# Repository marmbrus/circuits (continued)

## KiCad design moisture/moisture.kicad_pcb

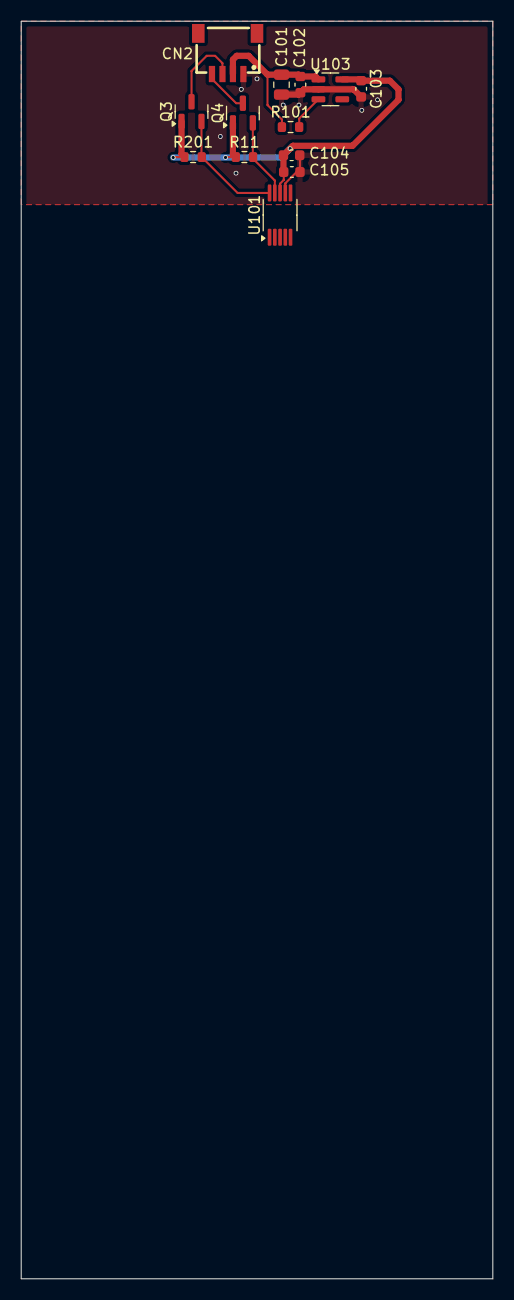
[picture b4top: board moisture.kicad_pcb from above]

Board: 4 copper layers, 45.0 x 120.0 mm, 13 parts (0 on the bottom side), 8 nets.

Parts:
C101: 10uF; C_0805_2012Metric
C102, C103, C104: 1uF; C_0603_1608Metric
C105: 100nF; C_0603_1608Metric
CN2: SM04B-SRSS-TB (LF)(SN); CONN-SMD_4P-P1.00_SM04B-SRSS-TB-LF-SN
Q3, Q4: BSS138; SOT-23
R11, R101, R201: 10k; R_0603_1608Metric
U101: FDC1004DGSR; MSOP-10_3x3mm_P0.5mm
U103: TLV75733PDBV; SOT-23-5

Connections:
/i2c/3V3: C103.1, C104.1, C105.1, Q3.1 (G), Q4.1 (G), R11.1, R201.1, U101.8 (VDD), U103.5 (OUT)
/i2c/5V: C101.1, C102.1, CN2.2, R101.1, U103.1 (IN)
/i2c/GND: C101.2, C102.2, C103.2, C104.2, C105.2, CN2.1, U101.7 (GND), U103.2 (GND)
/i2c/I2C.SCL: Q4.2 (S), R11.2, U101.9 (SCL)
/i2c/I2C.SDA: Q3.2 (S), R201.2, U101.10 (SDA)
unnamed: CN2.3, Q3.3 (D)
unnamed: CN2.4, Q4.3 (D)
unnamed: R101.2, U103.3 (EN)

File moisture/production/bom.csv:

Designator,Footprint,Quantity,Value,LCSC Part #
C101,0805,1,10uF,
"C102, C103, C104",0603,3,1uF,
C105,0603,1,100nF,
CN2,CONN-SMD_4P-P1.00_SM04B-SRSS-TB-LF-SN,1,SM04B-SRSS-TB (LF)(SN),C160404
"Q3, Q4",SOT-23,2,BSS138,
"R101, R11, R201",0603,3,10k,
U103,SOT-23-5,1,TLV75733PDBV,

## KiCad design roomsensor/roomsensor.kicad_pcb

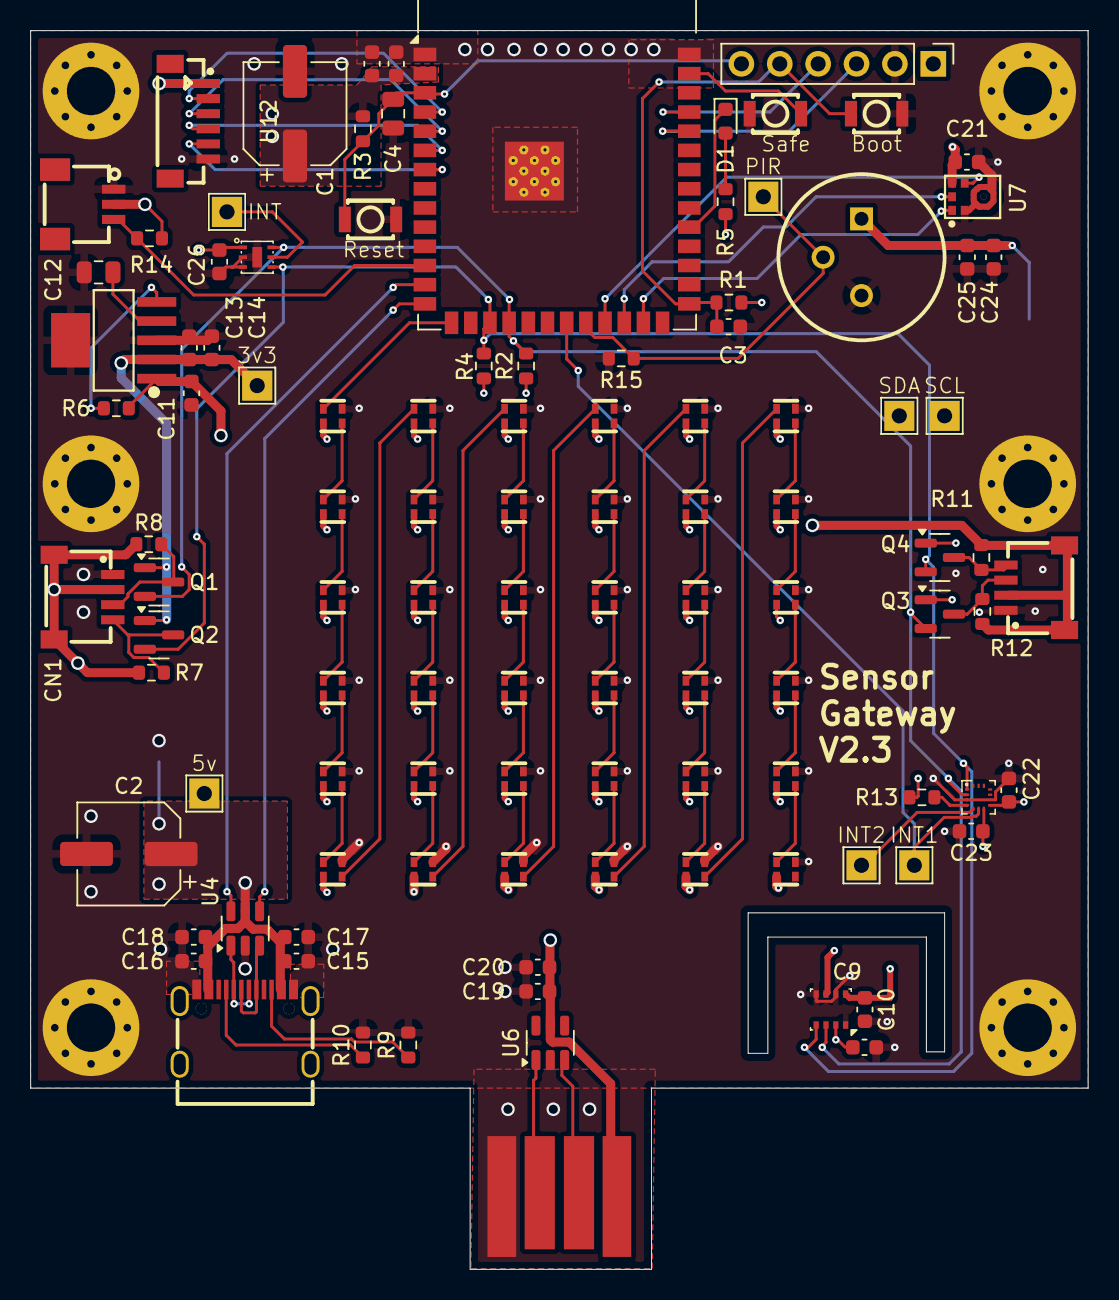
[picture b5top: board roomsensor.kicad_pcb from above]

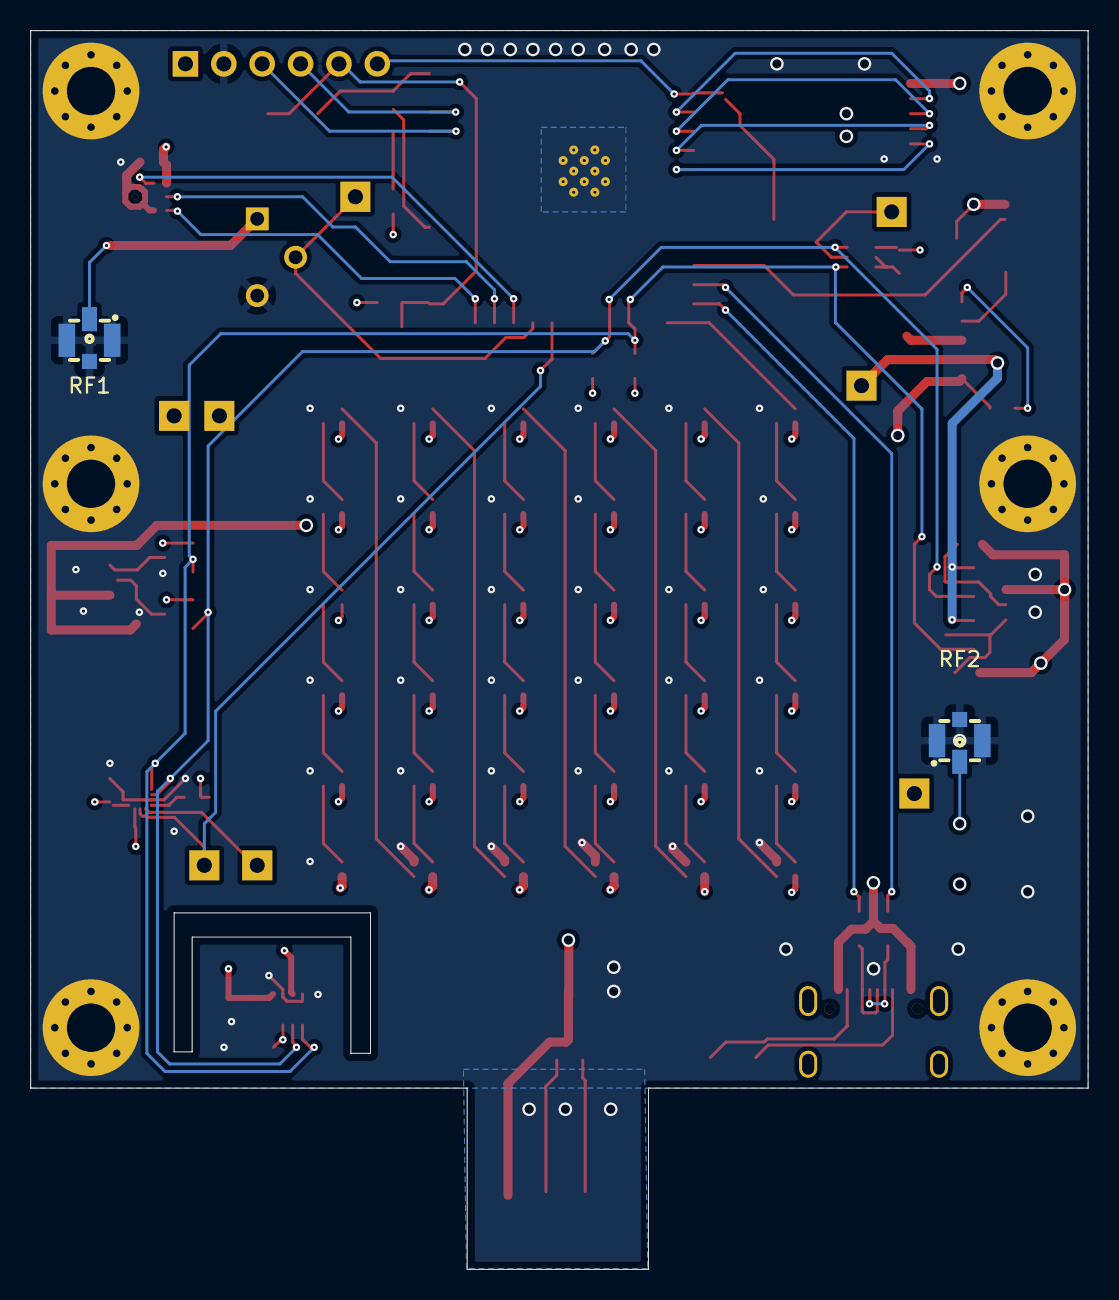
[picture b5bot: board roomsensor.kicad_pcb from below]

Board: 4 copper layers, 70.0 x 82.0 mm, 115 parts (2 on the bottom side), 75 nets.

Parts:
C1, C2: 47uF; CP_Elec_6.3x5.9
C3, C7, C11, C13, C14, C17, C18, C20, C24: 1uF; C_0603_1608Metric
C4: 10uF; C_0805_2012Metric
C8, C9, C10, C15, C16, C19, C21, C22, C23, C25, C26: 100nF; C_0603_1608Metric
C12: 10nF; C_0805_2012Metric
CN1, CN2: SM04B-SRSS-TB (LF)(SN); CONN-SMD_4P-P1.00_SM04B-SRSS-TB-LF-SN
D1: LED; LED_0603_1608Metric
H1, H2, H3, H4, H5, H6: MountingHole_Pad; MountingHole_3.2mm_M3_Pad_Via
J1: Conn_01x06; PinHeader_1x06_P2.54mm_Vertical
LED1, LED2, LED3, LED4, LED5, LED6, LED7, LED8, LED9, LED10, LED11, LED12, LED13, LED14, LED15, LED16, LED17, LED18, LED19, LED20, LED21, LED22, LED23, LED24, LED25, LED26, LED27, LED28, LED29, LED30, LED31, LED32, LED33, LED34, LED35, LED36: XL-1615RGBC-WS2812B-S; LED-SMD_4P-L1.6-W1.5_XL-1615RGBC-WS2812B-S
Q1, Q2, Q3, Q4: BSS138; SOT-23
R1, R2, R3, R4, R6, R7, R8, R11, R12, R13: 10k; R_0603_1608Metric
R5: 330; R_0603_1608Metric
R9, R10: 5.1k; R_0603_1608Metric
R14: 4.7k; R_0603_1608Metric
R15: 100k; R_0603_1608Metric
RF1, RF2: 73412-0110; ANT-SMD_73412-0110
SW1, SW2, SW3: KEY-SMD_B3U-1000PM
TP1, TP2, TP4, TP5, TP10, TP11, TP12, TP13: LabeledTestPoint
U1: ESP32-S3-WROOM-1-N16R8; ESP32-S3-WROOM-1
U2: BME280; Bosch_LGA-8_2.5x2.5mm_P0.65mm_ClockwisePinNumbering
U3: TPS73733DCQ_C5220270; SOT-223-6_L6.5-W3.5-P1.27-LS7.0-BR
U4, U6: USBLC6-2SC6; SOT-23-6
U5: usb-PCB
U7: ICS-43434_C5656610; MIC-SMD_6P-L3.5-W2.7-P0.90-BL
U8: LIS2DHTR; LGA-14_L2.0-W2.0-P0.35-BL
U9: SM03B-SRSS-TB(LF)(SN)(P); CONN-SMD_SM03B-SRSS-TB-LF-SN-P
U10: EKMC1601112; SENSOR-TH_EKMC1601111
U11: OPT3001DNPR; USON6_L2.1-W2.1-P0.65-BL-EP
U12: BM06B-SRSS-TB(LF)(SN); CONN-SMD-6P-P1.00_BM06B-SRSS-TB-LF-SN
USBC1: TYPE-C-31-M-12; USB-C_SMD-TYPE-C-31-M-12

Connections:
+5V: C2.1, C11.1, C15.1, C16.1, C17.1, C18.1, C19.1, C20.1, CN1.2, CN1.5, CN1.6, CN2.2, CN2.5, CN2.6, LED1.2 (VDD), LED2.2 (VDD), LED3.2 (VDD), LED4.2 (VDD), LED5.2 (VDD), LED6.2 (VDD), LED7.2 (VDD), LED8.2 (VDD), LED9.2 (VDD), LED10.2 (VDD), LED11.2 (VDD), LED12.2 (VDD), LED13.2 (VDD), LED14.2 (VDD), LED15.2 (VDD), LED16.2 (VDD), LED17.2 (VDD), LED18.2 (VDD), LED19.2 (VDD), LED20.2 (VDD), LED21.2 (VDD), LED22.2 (VDD), LED23.2 (VDD), LED24.2 (VDD), LED25.2 (VDD), LED26.2 (VDD), LED27.2 (VDD), LED28.2 (VDD), LED29.2 (VDD), LED30.2 (VDD), LED31.2 (VDD), LED32.2 (VDD), LED33.2 (VDD), LED34.2 (VDD), LED35.2 (VDD), LED36.2 (VDD), R6.1, R7.1, R8.1, R11.1, R12.1, RF2.2 (SIG), TP1.1, U3.1 (IN), U4.5 (VBUS), U5.1 (5V), U6.5 (VBUS), U12.1, USBC1.A4 (VBUS), USBC1.A9 (VBUS), USBC1.B4 (VBUS), USBC1.B9 (VBUS)
/3v3/3v3: C1.1, C7.1, C8.1, C9.1, C10.1, C13.1, C14.1, C21.1, C22.1, C23.1, C24.1, C25.1, C26.1, J1.1, Q1.1 (G), Q2.1 (G), Q3.1 (G), Q4.1 (G), R1.2, R2.1, R3.2, R4.1, R5.2, R13.1, R14.1, RF1.2 (SIG), TP2.1, U1.2 (3V3), U2.2 (CSB), U2.6 (VDDIO), U2.8 (VDD), U3.2 (OUT), U7.5 (VDD), U8.7 (VDD_IO), U8.8 (VDD), U9.2, U10.1 (VDD), U11.1 (VDD)
/accel/I2C.SCL: Q2.2 (S), Q4.2 (S), R4.2, TP11.1, U1.17 (IO9), U2.4 (SCK), U8.1 (SCL/SPC), U11.4 (SCL)
/accel/I2C.SDA: Q1.2 (S), Q3.2 (S), R2.2, TP10.1, U1.18 (IO10), U2.3 (SDI), U8.2 (SDA/SDI/SDO), U11.6 (SDA)
/accel/INT: TP12.1, U1.21 (IO13), U8.6 (INT1)
/esp32/I2S.SCK: U1.23 (IO21), U7.4 (SCK)
/esp32/I2S.SD: U1.24 (IO47), U7.6 (SD)
/esp32/I2S.WS: U1.25 (IO48), U7.1 (WS)
/esp32/LED: LED1.4 (DI), U1.15 (IO3)
/esp32/USB.DN: U1.13 (IO19), U4.6 (I/O1)
/esp32/USB.DP: U1.14 (IO20), U4.4 (I/O2)
/esp32/boot: C3.1, J1.5, R1.1, SW1.2, U1.27 (IO0)
/esp32/enable: C4.1, J1.6, R3.1, SW2.2, U1.3 (EN)
/esp32/motion: R15.1, TP4.1, U1.22 (IO14), U10.2 (OUT)
/esp32/rx: J1.3, U1.36 (RXD0)
/esp32/temp: R14.2, U1.12 (IO8), U9.3
/esp32/tx: J1.4, U1.37 (TXD0)
/leds/column1/DOUT: LED12.1 (DO), LED13.4 (DI)
/leds/column2/DOUT: LED18.1 (DO), LED19.4 (DI)
/leds/column3/DOUT: LED24.1 (DO), LED25.4 (DI)
/leds/column4/DOUT: LED30.1 (DO), LED31.4 (DI)
/leds/column/DOUT: LED6.1 (DO), LED7.4 (DI)
/usbc/DN: U4.1 (I/O1), USBC1.A7 (DN1), USBC1.B7 (DN2)
/usbc/DP: U4.3 (I/O2), USBC1.A6 (DP1), USBC1.B6 (DP2)
GND: C1.2, C2.2, C3.2, C4.2, C7.2, C8.2, C9.2, C10.2, C11.2, C12.2, C13.2, C14.2, C15.2, C16.2, C17.2, C18.2, C19.2, C20.2, C21.2, C22.2, C23.2, C24.2, C25.2, C26.2, CN1.1, CN2.1, H1.1, H2.1, H3.1, H4.1, H5.1, H6.1, J1.2, LED1.3 (GND), LED2.3 (GND), LED3.3 (GND), LED4.3 (GND), LED5.3 (GND), LED6.3 (GND), LED7.3 (GND), LED8.3 (GND), LED9.3 (GND), LED10.3 (GND), LED11.3 (GND), LED12.3 (GND), LED13.3 (GND), LED14.3 (GND), LED15.3 (GND), LED16.3 (GND), LED17.3 (GND), LED18.3 (GND), LED19.3 (GND), LED20.3 (GND), LED21.3 (GND), LED22.3 (GND), LED23.3 (GND), LED24.3 (GND), LED25.3 (GND), LED26.3 (GND), LED27.3 (GND), LED28.3 (GND), LED29.3 (GND), LED30.3 (GND), LED31.3 (GND), LED32.3 (GND), LED33.3 (GND), LED34.3 (GND), LED35.3 (GND), LED36.3 (GND), R9.2, R10.2, R15.2, RF1.1 (GND), RF1.3 (GND), RF1.4 (GND), RF2.1 (GND), RF2.3 (GND), RF2.4 (GND), SW1.1, SW2.1, SW3.1, U1.1 (GND), U1.40 (GND), U1.41 (GND), U2.1 (GND), U2.5 (SDO), U2.7 (GND), U3.3 (GND), U3.6 (GND), U4.2 (GND), U5.4 (GND), U6.2 (GND), U7.2 (LR), U7.3 (GND), U8.3 (SDO/SA0), U8.9 (GND), U9.1, U10.3 (GND), U11.2 (ADDR), U11.3 (GND), U11.7 (EP), U12.6, USBC1.A1 (GND), USBC1.A12 (GND), USBC1.B1 (GND), USBC1.B12 (GND)
unnamed: D1.2 (A), R5.1
unnamed: D1.1 (K), U1.31 (IO38)
unnamed: LED1.1 (DO), LED2.4 (DI)
unnamed: LED2.1 (DO), LED3.4 (DI)
unnamed: LED3.1 (DO), LED4.4 (DI)
unnamed: LED4.1 (DO), LED5.4 (DI)
unnamed: LED5.1 (DO), LED6.4 (DI)
unnamed: LED7.1 (DO), LED8.4 (DI)
unnamed: LED8.1 (DO), LED9.4 (DI)
unnamed: LED9.1 (DO), LED10.4 (DI)
unnamed: LED10.1 (DO), LED11.4 (DI)
unnamed: LED11.1 (DO), LED12.4 (DI)
unnamed: LED13.1 (DO), LED14.4 (DI)
unnamed: LED14.1 (DO), LED15.4 (DI)
unnamed: LED15.1 (DO), LED16.4 (DI)
unnamed: LED16.1 (DO), LED17.4 (DI)
unnamed: LED17.1 (DO), LED18.4 (DI)
unnamed: LED19.1 (DO), LED20.4 (DI)
unnamed: LED20.1 (DO), LED21.4 (DI)
unnamed: LED21.1 (DO), LED22.4 (DI)
unnamed: LED22.1 (DO), LED23.4 (DI)
unnamed: LED23.1 (DO), LED24.4 (DI)
unnamed: LED25.1 (DO), LED26.4 (DI)
unnamed: LED26.1 (DO), LED27.4 (DI)
unnamed: LED27.1 (DO), LED28.4 (DI)
unnamed: LED28.1 (DO), LED29.4 (DI)
unnamed: LED29.1 (DO), LED30.4 (DI)
unnamed: LED31.1 (DO), LED32.4 (DI)
unnamed: LED32.1 (DO), LED33.4 (DI)
unnamed: LED33.1 (DO), LED34.4 (DI)
unnamed: LED34.1 (DO), LED35.4 (DI)
unnamed: LED35.1 (DO), LED36.4 (DI)
unnamed: CN1.3, Q1.3 (D), R8.2
unnamed: CN1.4, Q2.3 (D), R7.2
unnamed: CN2.3, Q3.3 (D), R12.2
unnamed: CN2.4, Q4.3 (D), R11.2
unnamed: SW3.2, U1.39 (IO1)
unnamed: U1.4 (IO4), U12.2
unnamed: U1.5 (IO5), U12.3
unnamed: U1.6 (IO6), U12.4
unnamed: U1.7 (IO7), U12.5
unnamed: R6.2, U3.5 (EN)
unnamed: C12.1, U3.4 (NR/FB)
unnamed: U5.3 (D+), U6.1 (I/O1)
unnamed: U5.2 (D-), U6.3 (I/O2)
unnamed: R13.2, U8.4 (CS)
unnamed: TP13.1, U8.5 (INT2)
unnamed: TP5.1, U11.5 (INT)
unnamed: R10.1, USBC1.A5 (CC1)
unnamed: R9.1, USBC1.B5 (CC2)

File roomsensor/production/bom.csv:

Designator,Footprint,Quantity,Value,LCSC Part #
"C1, C2",CP_Elec_6.3x5.9,2,47uF,C264034
"C10, C21, C22, C23, C9",0603,5,100nF,
"C11, C13, C14, C17, C18, C20, C24, C3",0603,8,1uF,
C12,0805,1,10nF,
"C15, C16, C19, C25, C26, C8",0603,6,100nF,
C4,0805,1,10uF,
C7,0603,1,1uF,
"CN1, CN2",CONN-SMD_4P-P1.00_SM04B-SRSS-TB-LF-SN,2,SM04B-SRSS-TB (LF)(SN),C160404
D1,0603,1,LED,C2290
"LED1, LED10, LED11, LED12, LED13, LED14, LED15, LED16, LED17, LED18, LED19, LED2, LED20, LED21, LED22, LED23, LED24, LED25, LED26, LED27, LED28, LED29, LED3, LED30, LED31, LED32, LED33, LED34, LED35, LED36, LED4, LED5, LED6, LED7, LED8, LED9",LED-SMD_4P-L1.6-W1.5_XL-1615RGBC-WS2812B-S,36,XL-1615RGBC-WS2812B-S,C41413180
"Q1, Q2, Q3, Q4",SOT-23,4,BSS138,
"R1, R11, R12, R13, R2, R3, R4, R6, R7, R8",0603,10,10k,
"R10, R9",0603,2,5.1k,
R14,0603,1,4.7k,
R15,0603,1,100k,
R5,0603,1,330,
"SW1, SW2, SW3",KEY-SMD_B3U-1000PM,3,KEY-SMD_B3U-1000PM,C231329
U1,ESP32-S3-WROOM-1,1,ESP32-S3-WROOM-1-N16R8,
U10,SENSOR-TH_EKMC1601111,1,EKMC1601112,C5128270
U11,USON6_L2.1-W2.1-P0.65-BL-EP,1,OPT3001DNPR,C90462
U12,CONN-SMD-6P-P1.00_BM06B-SRSS-TB-LF-SN,1,BM06B-SRSS-TB(LF)(SN),C160392
U2,Bosch_LGA-8_2.5x2.5mm_P0.65mm_ClockwisePinNumbering,1,BME280,
U3,SOT-223-6_L6.5-W3.5-P1.27-LS7.0-BR,1,TPS73733DCQ_C5220270,C5220270
"U4, U6",SOT-23-6,2,USBLC6-2SC6,
U7,MIC-SMD_6P-L3.5-W2.7-P0.90-BL,1,ICS-43434_C5656610,C5656610
U8,LGA-14_L2.0-W2.0-P0.35-BL,1,LIS2DHTR,C155670
U9,CONN-SMD_SM03B-SRSS-TB-LF-SN-P,1,SM03B-SRSS-TB(LF)(SN)(P),C160403
USBC1,USB-C_SMD-TYPE-C-31-M-12,1,TYPE-C-31-M-12,C165948

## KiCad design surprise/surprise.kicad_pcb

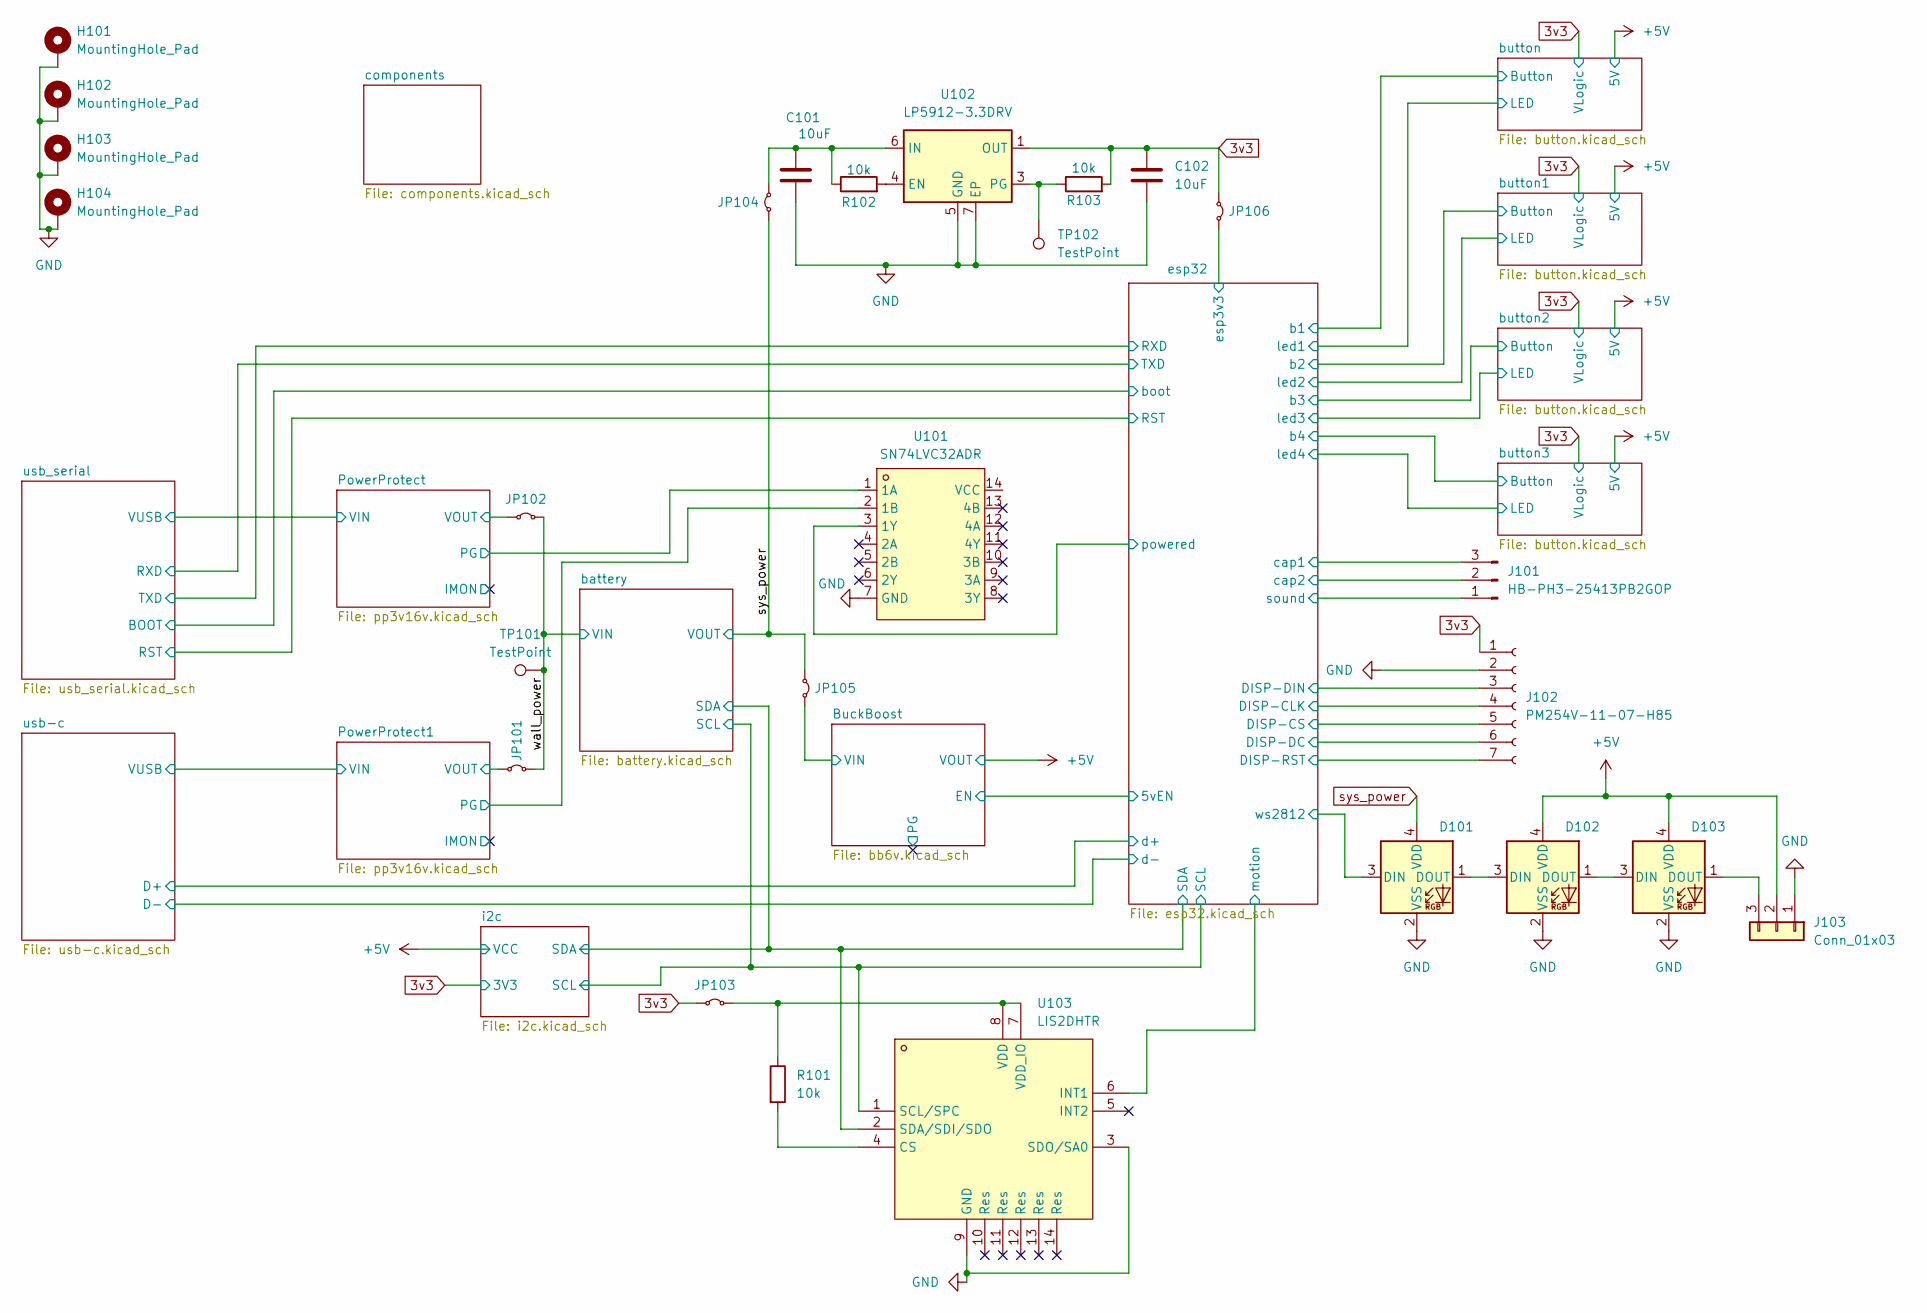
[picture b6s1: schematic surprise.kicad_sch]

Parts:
C101, C102: 10uF; C_0603_1608Metric
D101, D102, D103: WS2812B-2020; LED_WS2812B-2020_PLCC4_2.0x2.0mm
H101, H102, H103, H104: MountingHole_Pad; MountingHole_3.2mm_M3_Pad_Via
J101: HB-PH3-25413PB2GOP; PinHeader_1x03_P2.54mm_Vertical
J102: PM254V-11-07-H85; PinHeader_1x07_P2.54mm_Vertical
J103: Conn_01x03; JST_PH_B3B-PH-K_1x03_P2.00mm_Vertical; LCSC Part C131339
JP101, JP102, JP103, JP104, JP105, JP106: JP1; SolderJumper-2_P1.3mm_Bridged_RoundedPad1.0x1.5mm
R101, R102, R103: 10k; R_0603_1608Metric
TP101, TP102: TestPoint; Pin_D1.0mm_L10.0mm
U101: SN74LVC32ADR; SOIC-14_L8.7-W3.9-P1.27-LS6.0-BL; LCSC Part C7852
U102: LP5912-3.3DRV; WSON-6-1EP_2x2mm_P0.65mm_EP1x1.6mm_ThermalVias
U103: LIS2DHTR; LGA-14_L2.0-W2.0-P0.35-BL; LCSC Part C155670

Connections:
3v3: C102.1, J102.1, JP103.1 (A), JP106.1 (A), R103.2, U102.1 (OUT); also elsewhere on the board
+5V: D102.4 (VDD), D103.4 (VDD), J103.2; also elsewhere on the board
/BuckBoost/VIN: JP105.2 (B); also elsewhere on the board
/PowerProtect1/PG: U101.2 (1B); also elsewhere on the board
/PowerProtect1/VOUT: JP101.1 (A); also elsewhere on the board
/PowerProtect/PG: U101.1 (1A); also elsewhere on the board
/PowerProtect/VOUT: JP102.1 (A); also elsewhere on the board
/battery/SCL: U103.1 (SCL/SPC); also elsewhere on the board
/battery/SDA: U103.2 (SDA/SDI/SDO); also elsewhere on the board
/esp32/DISP-CLK: J102.4; also elsewhere on the board
/esp32/DISP-CS: J102.5; also elsewhere on the board
/esp32/DISP-DC: J102.6; also elsewhere on the board
/esp32/DISP-DIN: J102.3; also elsewhere on the board
/esp32/DISP-RST: J102.7; also elsewhere on the board
/esp32/cap1: J101.3; also elsewhere on the board
/esp32/cap2: J101.2; also elsewhere on the board
/esp32/esp3v3: JP106.2 (B); also elsewhere on the board
/esp32/motion: U103.6 (INT1); also elsewhere on the board
/esp32/powered: U101.3 (1Y); also elsewhere on the board
/esp32/sound: J101.1; also elsewhere on the board
/esp32/ws2812: D101.3 (DIN); also elsewhere on the board
/wall_power: JP101.2 (B), JP102.2 (B), TP101.1; also elsewhere on the board
GND: C101.2, C102.2, D101.2 (VSS), D102.2 (VSS), D103.2 (VSS), H101.1, H102.1, H103.1, H104.1, J102.2, J103.1, U101.7 (GND), U102.5 (GND), U102.7 (EP), U103.3 (SDO/SA0), U103.9 (GND); also elsewhere on the board
unnamed: D101.1 (DOUT), D102.3 (DIN)
unnamed: D102.1 (DOUT), D103.3 (DIN)
unnamed: D103.1 (DOUT), J103.3
unnamed: JP103.2 (B), R101.1, U103.7 (VDD_IO), U103.8 (VDD)
unnamed: C101.1, JP104.2 (B), R102.1, U102.6 (IN)
unnamed: R102.2, U102.4 (EN)
unnamed: R103.1, TP102.1, U102.3 (PG)
unnamed: R101.2, U103.4 (CS)
sys_power: D101.4 (VDD), JP104.1 (A), JP105.1 (A); also elsewhere on the board

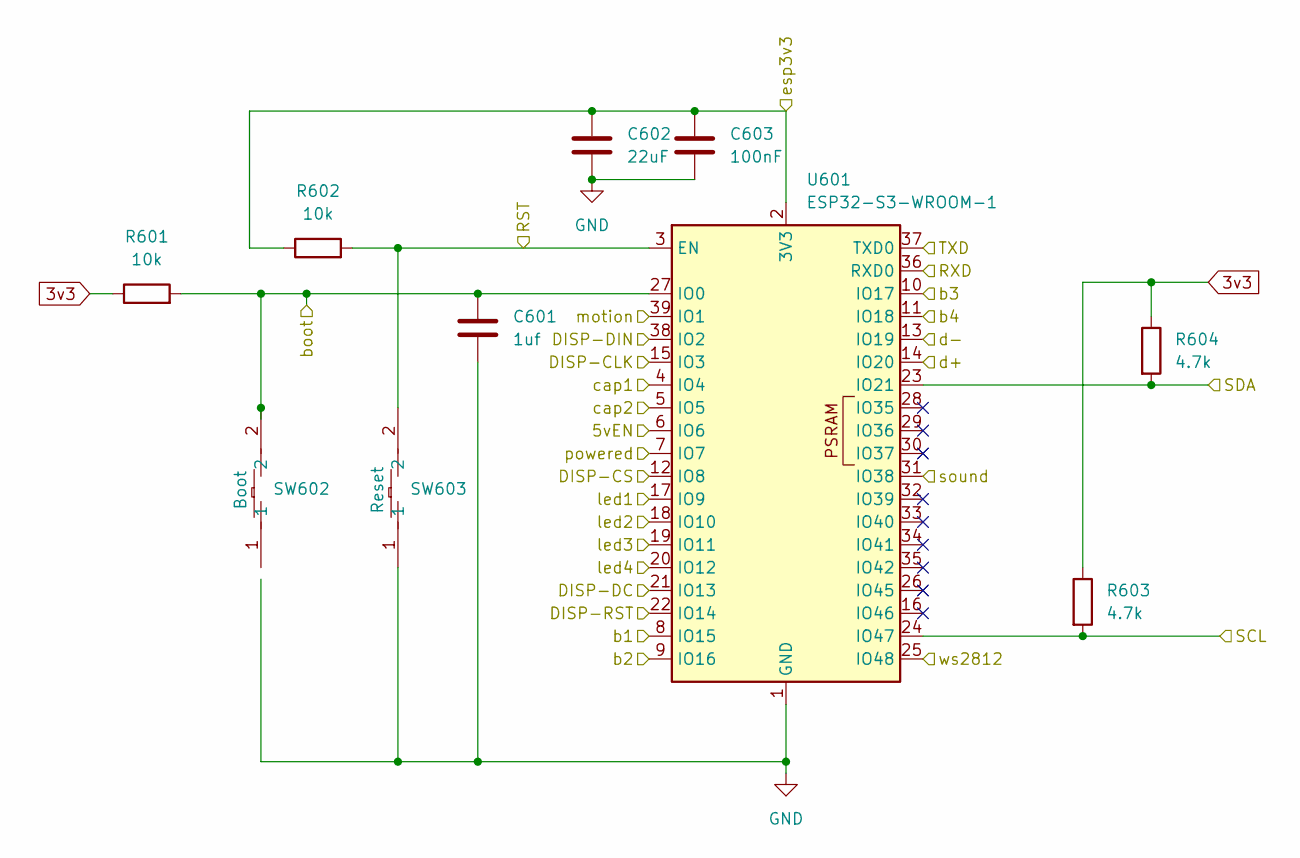
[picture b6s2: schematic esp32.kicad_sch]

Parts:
C601: 1uf; C_0603_1608Metric
C602: 22uF; C_0603_1608Metric
C603: 100nF; C_0603_1608Metric
R601, R602: 10k; R_0603_1608Metric
R603, R604: 4.7k; R_0603_1608Metric
SW602, SW603: KEY-SMD_B3U-1000PM; LCSC Part C231329
U601: ESP32-S3-WROOM-1

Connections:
3v3: R601.1, R603.1, R604.1; also elsewhere on the board
/BuckBoost/EN: U601.6 (IO6); also elsewhere on the board
/battery/SCL: R603.2, U601.24 (IO47); also elsewhere on the board
/battery/SDA: R604.2, U601.23 (IO21); also elsewhere on the board
/button1/Button: U601.9 (IO16); also elsewhere on the board
/button1/LED: U601.18 (IO10); also elsewhere on the board
/button2/Button: U601.10 (IO17); also elsewhere on the board
/button2/LED: U601.19 (IO11); also elsewhere on the board
/button3/Button: U601.11 (IO18); also elsewhere on the board
/button3/LED: U601.20 (IO12); also elsewhere on the board
/button/Button: U601.8 (IO15); also elsewhere on the board
/button/LED: U601.17 (IO9); also elsewhere on the board
/esp32/DISP-CLK: U601.15 (IO3); also elsewhere on the board
/esp32/DISP-CS: U601.12 (IO8); also elsewhere on the board
/esp32/DISP-DC: U601.21 (IO13); also elsewhere on the board
/esp32/DISP-DIN: U601.38 (IO2); also elsewhere on the board
/esp32/DISP-RST: U601.22 (IO14); also elsewhere on the board
/esp32/RST: R602.2, SW603.2, U601.3 (EN); also elsewhere on the board
/esp32/RXD: U601.36 (RXD0); also elsewhere on the board
/esp32/TXD: U601.37 (TXD0); also elsewhere on the board
/esp32/boot: C601.1, R601.2, SW602.2, U601.27 (IO0); also elsewhere on the board
/esp32/cap1: U601.4 (IO4); also elsewhere on the board
/esp32/cap2: U601.5 (IO5); also elsewhere on the board
/esp32/d+: U601.14 (IO20); also elsewhere on the board
/esp32/d-: U601.13 (IO19); also elsewhere on the board
/esp32/esp3v3: C602.1, C603.1, R602.1, U601.2 (3V3); also elsewhere on the board
/esp32/motion: U601.39 (IO1); also elsewhere on the board
/esp32/powered: U601.7 (IO7); also elsewhere on the board
/esp32/sound: U601.31 (IO38); also elsewhere on the board
/esp32/ws2812: U601.25 (IO48); also elsewhere on the board
GND: C601.2, C602.2, C603.2, SW603.1, U601.1 (GND), U601.40 (GND), U601.41 (GND); also elsewhere on the board

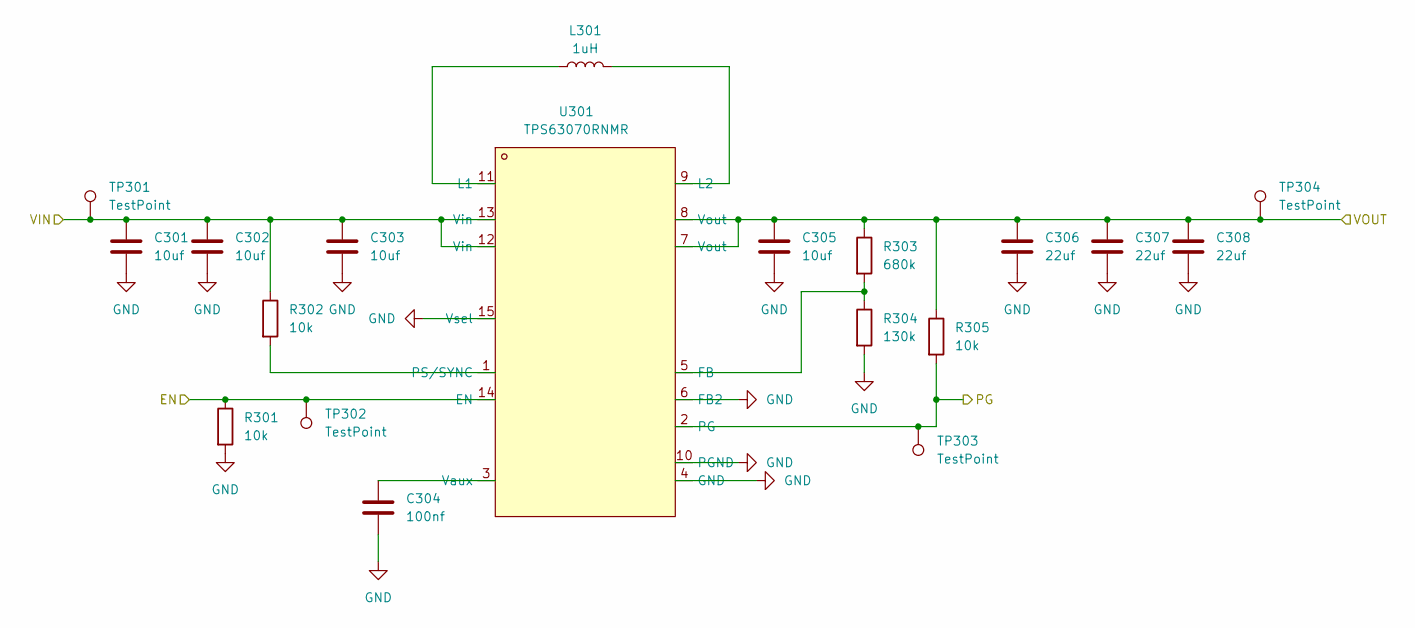
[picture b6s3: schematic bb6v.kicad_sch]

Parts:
C301, C302: 10uf; C_0805_2012Metric
C303, C305: 10uf; C_0603_1608Metric
C304: 100nf; C_0603_1608Metric
C306, C307, C308: 22uf; C_0805_2012Metric
L301: 1uH; L_Coilcraft_XAL4020-XXX; LCSC Part C4555951
R301, R302, R305: 10k; R_0603_1608Metric
R303: 680k; R_0603_1608Metric
R304: 130k; R_0603_1608Metric
TP301, TP302, TP303, TP304: TestPoint; Pin_D1.0mm_L10.0mm
U301: TPS63070RNMR; VQFN-HR-15_L3.0-W2.5-P0.50-BL_TPS63070RNMR; LCSC Part C109322

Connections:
+5V: C305.1, C306.1, C307.1, C308.1, R303.1, R305.1, TP304.1, U301.7 (Vout), U301.8 (Vout); also elsewhere on the board
/BuckBoost/EN: R301.1, TP302.1, U301.14 (EN); also elsewhere on the board
/BuckBoost/PG: R305.2, TP303.1, U301.2 (PG)
/BuckBoost/VIN: C301.1, C302.1, C303.1, R302.1, TP301.1, U301.12 (Vin), U301.13 (Vin); also elsewhere on the board
GND: C301.2, C302.2, C303.2, C304.2, C305.2, C306.2, C307.2, C308.2, R301.2, R304.2, U301.4 (GND), U301.6 (FB2), U301.10 (PGND), U301.15 (Vsel); also elsewhere on the board
unnamed: R303.2, R304.1, U301.5 (FB)
unnamed: L301.1, U301.11 (L1)
unnamed: L301.2, U301.9 (L2)
unnamed: R302.2, U301.1 (PS/SYNC)
unnamed: C304.1, U301.3 (Vaux)

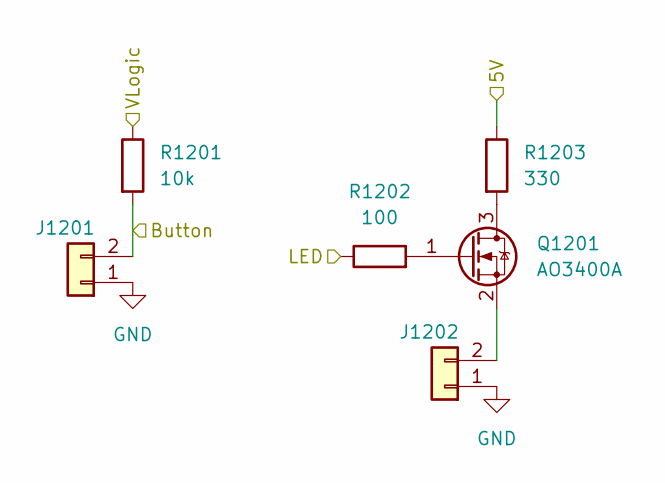
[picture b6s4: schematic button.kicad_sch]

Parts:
J1201, J1202: Conn_01x02; JST_XH_B2B-XH-A_1x02_P2.50mm_Vertical; LCSC Part C158012
Q1201: AO3400A; SOT-23
R1201: 10k; R_0603_1608Metric
R1202: 100; R_0603_1608Metric
R1203: 330; R_0603_1608Metric

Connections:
3v3: R1201.1; also elsewhere on the board
+5V: R1203.1; also elsewhere on the board
/button3/Button: J1201.2, R1201.2; also elsewhere on the board
/button3/LED: R1202.1; also elsewhere on the board
GND: J1201.1, J1202.1; also elsewhere on the board
unnamed: J1202.2, Q1201.2 (S)
unnamed: Q1201.3 (D), R1203.2
unnamed: Q1201.1 (G), R1202.2

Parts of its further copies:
J801, J802, J1001, J1002, J1101, J1102: Conn_01x02; JST_XH_B2B-XH-A_1x02_P2.50mm_Vertical; LCSC Part C158012
Q801, Q1001, Q1101: AO3400A; SOT-23
R801, R1001, R1101: 10k; R_0603_1608Metric
R802, R1002, R1102: 100; R_0603_1608Metric
R803, R1003, R1103: 330; R_0603_1608Metric

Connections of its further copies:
3v3: R801.1, R1001.1, R1101.1; also elsewhere on the board
+5V: R803.1, R1003.1, R1103.1; also elsewhere on the board
/button1/Button: J801.2, R801.2; also elsewhere on the board
/button1/LED: R802.1; also elsewhere on the board
/button2/Button: J1101.2, R1101.2; also elsewhere on the board
/button2/LED: R1102.1; also elsewhere on the board
/button/Button: J1001.2, R1001.2; also elsewhere on the board
/button/LED: R1002.1; also elsewhere on the board
GND: J801.1, J802.1, J1001.1, J1002.1, J1101.1, J1102.1; also elsewhere on the board
unnamed: J802.2, Q801.2 (S)
unnamed: J1002.2, Q1001.2 (S)
unnamed: J1102.2, Q1101.2 (S)
unnamed: Q801.3 (D), R803.2
unnamed: Q801.1 (G), R802.2
unnamed: Q1001.3 (D), R1003.2
unnamed: Q1001.1 (G), R1002.2
unnamed: Q1101.3 (D), R1103.2
unnamed: Q1101.1 (G), R1102.2

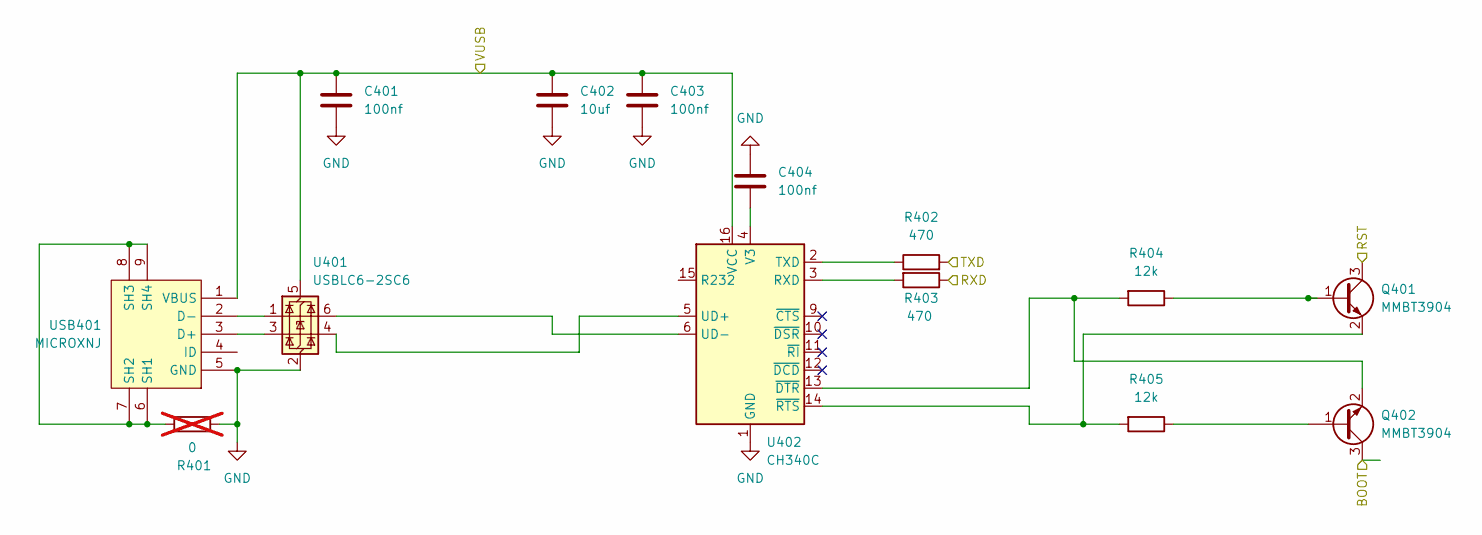
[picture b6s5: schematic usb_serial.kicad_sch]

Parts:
C401, C403, C404: 100nf; C_0603_1608Metric
C402: 10uf; C_0603_1608Metric
Q401, Q402: MMBT3904; SOT-23
R401: 0; R_0603_1608Metric; not fitted
R402, R403: 470; R_0603_1608Metric
R404, R405: 12k; R_0603_1608Metric
U401: USBLC6-2SC6; SOT-23-6
U402: CH340C; SOIC-16_3.9x9.9mm_P1.27mm
USB401: MICROXNJ; MICRO-USB-SMD_MICROXNJ; LCSC Part C404969

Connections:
/PowerProtect/VIN: C401.1, C402.1, C403.1, U401.5 (VBUS), U402.16 (VCC), USB401.1 (VBUS); also elsewhere on the board
/esp32/RST: Q401.3 (C); also elsewhere on the board
/esp32/RXD: R402.2; also elsewhere on the board
/esp32/TXD: R403.1; also elsewhere on the board
/esp32/boot: Q402.3 (C); also elsewhere on the board
GND: C401.2, C402.2, C403.2, C404.1, R401.2, U401.2 (GND), U402.1 (GND), USB401.5 (GND); also elsewhere on the board
unnamed: Q401.1 (B), R404.1
unnamed: Q401.2 (E), R405.2, U402.14 (~RTS)
unnamed: Q402.1 (B), R405.1
unnamed: Q402.2 (E), R404.2, U402.13 (~DTR)
unnamed: R403.2, U402.3 (RXD)
unnamed: R402.1, U402.2 (TXD)
unnamed: U401.4 (I/O2), U402.5 (UD+)
unnamed: U401.6 (I/O1), U402.6 (UD-)
unnamed: C404.2, U402.4 (V3)
unnamed: U401.3 (I/O2), USB401.3 (D+)
unnamed: U401.1 (I/O1), USB401.2 (D-)
unnamed: R401.1, USB401.6 (SH1), USB401.7 (SH2), USB401.8 (SH3), USB401.9 (SH4)

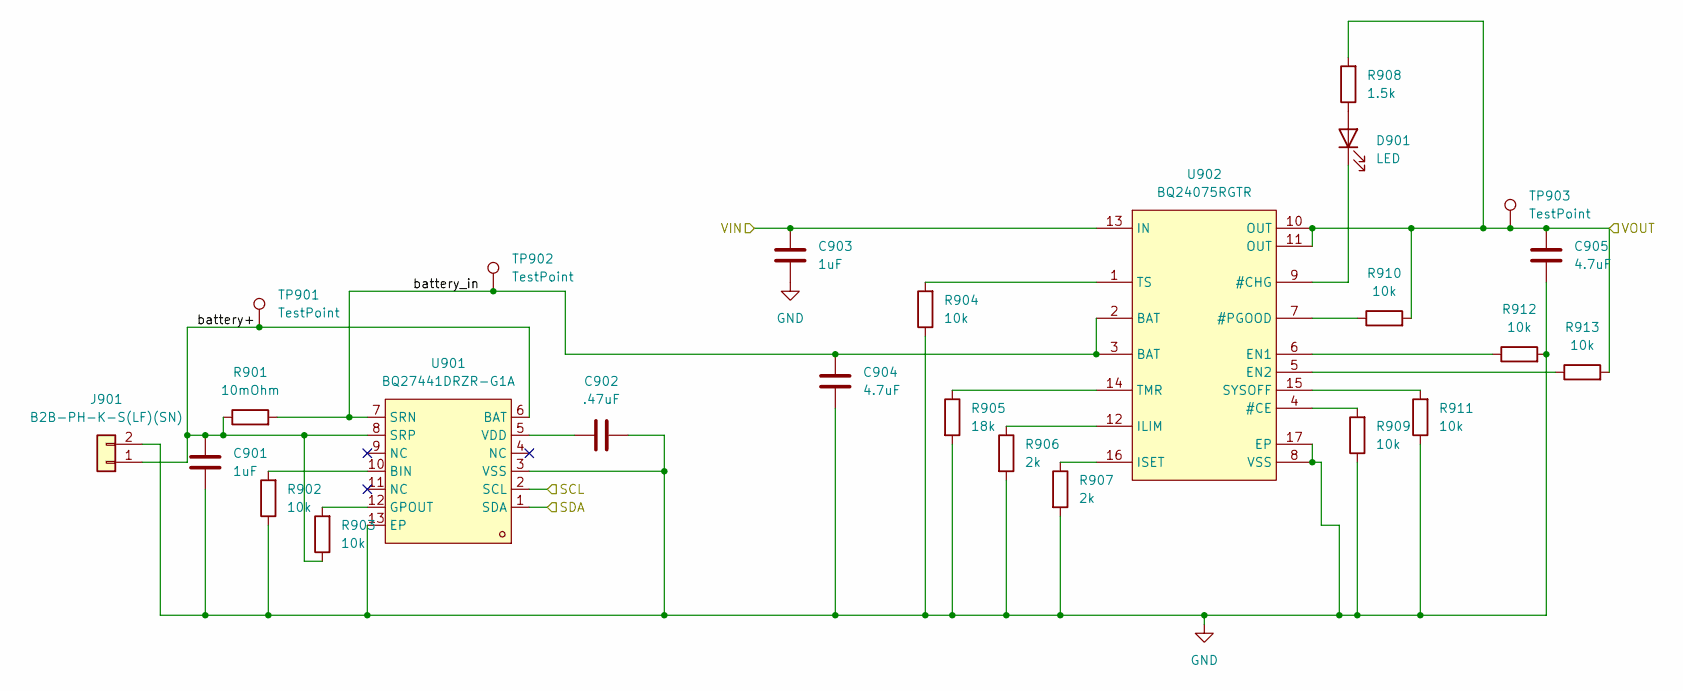
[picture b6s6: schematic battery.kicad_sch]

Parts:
C901, C903: 1uF; C_0603_1608Metric
C902: .47uF; C_0603_1608Metric
C904, C905: 4.7uF; C_0603_1608Metric
D901: LED; LED_0603_1608Metric; LCSC Part C2286
J901: B2B-PH-K-S(LF)(SN); JST_PH_B2B-PH-K_1x02_P2.00mm_Vertical
R901: 10mOhm; R_2512_6332Metric; LCSC Part Number C5121115
R902, R903, R904, R909, R910, R911, R912, R913: 10k; R_0603_1608Metric
R905: 18k; R_0603_1608Metric
R906, R907: 2k; R_0603_1608Metric
R908: 1.5k; R_0603_1608Metric
TP901, TP902, TP903: TestPoint; Pin_D1.0mm_L10.0mm
U901: BQ27441DRZR-G1A; SON-12_L4.0-W2.5-P0.40-BL-EP; LCSC Part C473397
U902: BQ24075RGTR; QFN-16_L3.0-W3.0-P0.50-TL-EP1.7; LCSC Part C15464

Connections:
/battery/SCL: U901.2 (SCL); also elsewhere on the board
/battery/SDA: U901.1 (SDA); also elsewhere on the board
/battery/battery+: C901.2, J901.1, R901.1, R903.1, TP901.1, U901.6 (BAT), U901.8 (SRP)
/battery/battery_in: C904.1, R901.2, TP902.1, U901.7 (SRN), U902.2 (BAT), U902.3 (BAT)
/wall_power: C903.1, U902.13 (IN); also elsewhere on the board
GND: C901.1, C902.2, C903.2, C904.2, C905.2, J901.2, R902.1, R904.1, R905.2, R906.2, R907.2, R909.1, R911.1, R912.2, U901.3 (VSS), U901.13 (EP), U902.8 (VSS), U902.17 (EP); also elsewhere on the board
unnamed: D901.2 (A), R908.1
unnamed: D901.1 (K), U902.9 (#CHG)
unnamed: R902.2, U901.10 (BIN)
unnamed: R903.2, U901.12 (GPOUT)
unnamed: C902.1, U901.5 (VDD)
unnamed: R909.2, U902.4 (#CE)
unnamed: R910.1, U902.7 (#PGOOD)
unnamed: R912.1, U902.6 (EN1)
unnamed: R913.1, U902.5 (EN2)
unnamed: R906.1, U902.12 (ILIM)
unnamed: R907.1, U902.16 (ISET)
unnamed: R911.2, U902.15 (SYSOFF)
unnamed: R905.1, U902.14 (TMR)
unnamed: R904.2, U902.1 (TS)
sys_power: C905.1, R908.2, R910.2, R913.2, TP903.1, U902.10 (OUT), U902.11 (OUT); also elsewhere on the board

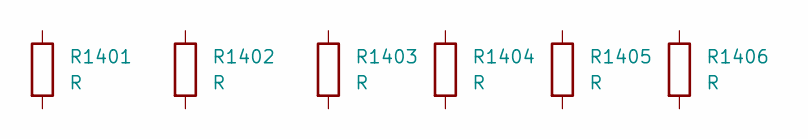
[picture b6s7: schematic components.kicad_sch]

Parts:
R1401: R; R_0201_0603Metric
R1402: R; R_0402_1005Metric
R1403: R; R_0603_1608Metric
R1404: R; R_0805_2012Metric
R1405: R; R_1206_3216Metric
R1406: R; R_2512_6332Metric
